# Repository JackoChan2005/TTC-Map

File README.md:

# TTC Map

A Toronto rail explorer and ESP32 LED display built around one transit-state API.
The web map shows Lines 1, 2, 4, 5 and 6 over OpenStreetMap, with route search,
station details, directional markers and a schematic view.

The project implements GTFS import and validation, bounded NTAS polling, estimated
train positions, a shared web/LED state model, the browser interface and firmware
for an eight-LED board revision. Contributor history is available in Git; individual
ownership and asset permissions are documented in [docs/ASSETS.md](docs/ASSETS.md).

The image records a real-data session on September 12, 2026; it is not a live feed.

```text
Toronto Open Data GTFS -> validated SQLite schedules/topology --+
TTC NTAS countdowns -> per-line snapshots and interpolation ----+-> map state
                                                               |-> web explorer
                                                               +-> ESP32 LED frame
```

Python/FastAPI serves the vanilla JavaScript/SVG frontend. SQLite, pandas and
HTTPX handle data; ESP-IDF/PlatformIO builds the firmware. There is no frontend
build step and no Node server.

## What the map means

- Filled arrows are NTAS-backed estimates; outlined arrows are scheduled estimates.
  Neither is GPS. Routes connect station coordinates approximately, not surveyed tracks.
- Lines 1/2/4 use NTAS when healthy. Line 5 is scheduled unless explicitly enabled
  after [coverage validation](docs/LINE_5_6.md); Line 6 is schedule-only.
- Direction follows API travel order. Unknown direction uses a neutral marker.
- Departures are scheduled, within a two-minute line-wide window capped at 200 rows.
  Service alerts, live station arrival boards and journey planning are unavailable.
- Data health does not imply normal TTC operations. Failed state requests clear
  train markers; a missing street background leaves the transit overlay usable.

## Run on Windows

Install [uv](https://docs.astral.sh/uv/getting-started/installation/), clone this
repository, then double-click `start.bat` or run it from PowerShell:

```powershell
.\start.bat
```

The launcher installs the locked dependencies and starts the server. It keeps
Python packages in `%LOCALAPPDATA%\TTC-Map\venv`, outside OneDrive. Python 3.13 is
selected by `.python-version`; uv can download it if needed. Do not repair or
reuse an old OneDrive-managed `.venv` to run this launcher.

Open <http://localhost:8000> for the map, `/search/` for timetable search, and
`/docs` or `/redoc` for the local interactive API reference. Stop with Ctrl+C.
For another port: `.\start.bat serve --port 8001`.

[Windows setup and clean-checkout verification](docs/SETUP.md) includes manual
commands, separate-checkout environments and offline rehearsal.

## macOS / Linux

Install [uv](https://docs.astral.sh/uv/getting-started/installation/), then open a
terminal in this repository and run:

```sh
./start.command
```

On macOS you can also double-click `start.command`. The launcher installs the
locked dependencies into `.venv` and starts the server. Open
<http://localhost:8000> and stop with Ctrl+C. Use
`./start.command serve --port 8001` for another port or `./start.command refresh`
for a feed check. If an extracted archive loses executable permissions, run
`bash start.command`.

Equivalent manual commands:

```sh
uv sync --locked
uv run --no-sync ttcmap serve
```

Python 3.12+ is supported by the package; the repository pins 3.13 for development.
Use one worker and a local SQLite database. Linux startup has been checked under
Ubuntu 24.04 (WSL2); macOS runtime and physical hardware validation remain separate
checks. See [setup verification](docs/SETUP.md#macos--linux).

## Commands

Run these after the platform-specific setup. On Windows, set
`$env:UV_PROJECT_ENVIRONMENT = "$env:LOCALAPPDATA\TTC-Map\venv"` first, or use
`.\start.bat refresh` for a feed check.

| Command | Purpose |
|---|---|
| `uv run --no-sync ttcmap refresh` | Check/rebuild the feed; add `--force` for a forced rebuild |
| `uv run --no-sync ttcmap build-network` | Regenerate exports from the verified cache |
| `uv run --no-sync pytest` | Backend tests |
| `uv run --no-sync ruff check src tests` | Python lint |
| `node --test tests/web/*.test.mjs` | Frontend unit tests, optional Node.js |
| `node scripts/build-schematic.mjs` | Regenerate schematic after network export |

Browser tests use a pinned optional Playwright install; see [SETUP.md](docs/SETUP.md).
There is no separate JavaScript build, type-checker or linter configured.

## API and structure

The local API reference reads `/openapi.json` and can send GET requests without
external scripts. All transit routes are below `/api/v1`:

| GET endpoint | Data |
|---|---|
| `/health`, `/gtfs/status` | Dataset and per-line source diagnostics |
| `/map-config` | Matching generation, network and schematic |
| `/network`, `/layout/{name}` | Topology or an individual layout |
| `/map-state` | Estimated positions; source and optional time selection |
| `/departures?route=1` | Scheduled departure window |
| `/led-state`, `/led-state.bin` | Board frame as JSON or packed bits |

Refresh is CLI-only. The former `POST /api/v1/gtfs/refresh` is removed so a viewer
cannot trigger an expensive rebuild. The web refresh button reloads read endpoints.

| Directory | Purpose |
|---|---|
| `src/ttcmap/` | API, GTFS pipeline, source selection and LED renderer |
| `web/` | Explorer, timetable and local API reference |
| `shared/` | Reviewed station identities and generated network/layout exports |
| `firmware/` | ESP-IDF firmware; local Wi-Fi settings are gitignored |
| `hardware/` | Integrated KiCad design and eight-LED board map |
| `tests/`, `scripts/` | Validation and schematic generation |
| `data/` | Ignored feeds, database, local validation and private asset archive |

Run from an editable repository checkout. A standalone wheel does not include the
web/shared/hardware resources and is not a supported deployment package.

## Configuration and troubleshooting

Copy `.env.example` to `.env` for optional overrides; all fields are in
`src/ttcmap/config.py`. Local paths resolve against the checkout. For OneDrive
installations that also need database isolation, configure `DATA_DIR` and `DB_PATH`
to local storage. Cloud synchronization is not multi-host database coordination.

- **Port occupied:** use another port with the launcher/CLI.
- **Transit data unavailable:** check `/api/v1/health` and refresh logs. First import,
  expired schedules or a failed upgrade can cause 503 responses.
- **Scheduled labels:** live observations may be unavailable or disabled for that line.
- **Street map unavailable:** use the schematic; OSM tiles are an external service.
- **Firmware connection:** follow [ESP32_SMOKE_TEST.md](docs/ESP32_SMOKE_TEST.md).
  The eight-LED revision does not represent a fully wired station network.

See [ARCHITECTURE.md](docs/ARCHITECTURE.md), [UI_API_AUDIT.md](docs/UI_API_AUDIT.md),
[validation results](docs/UI_VALIDATION.md) and [asset/publication status](docs/ASSETS.md).

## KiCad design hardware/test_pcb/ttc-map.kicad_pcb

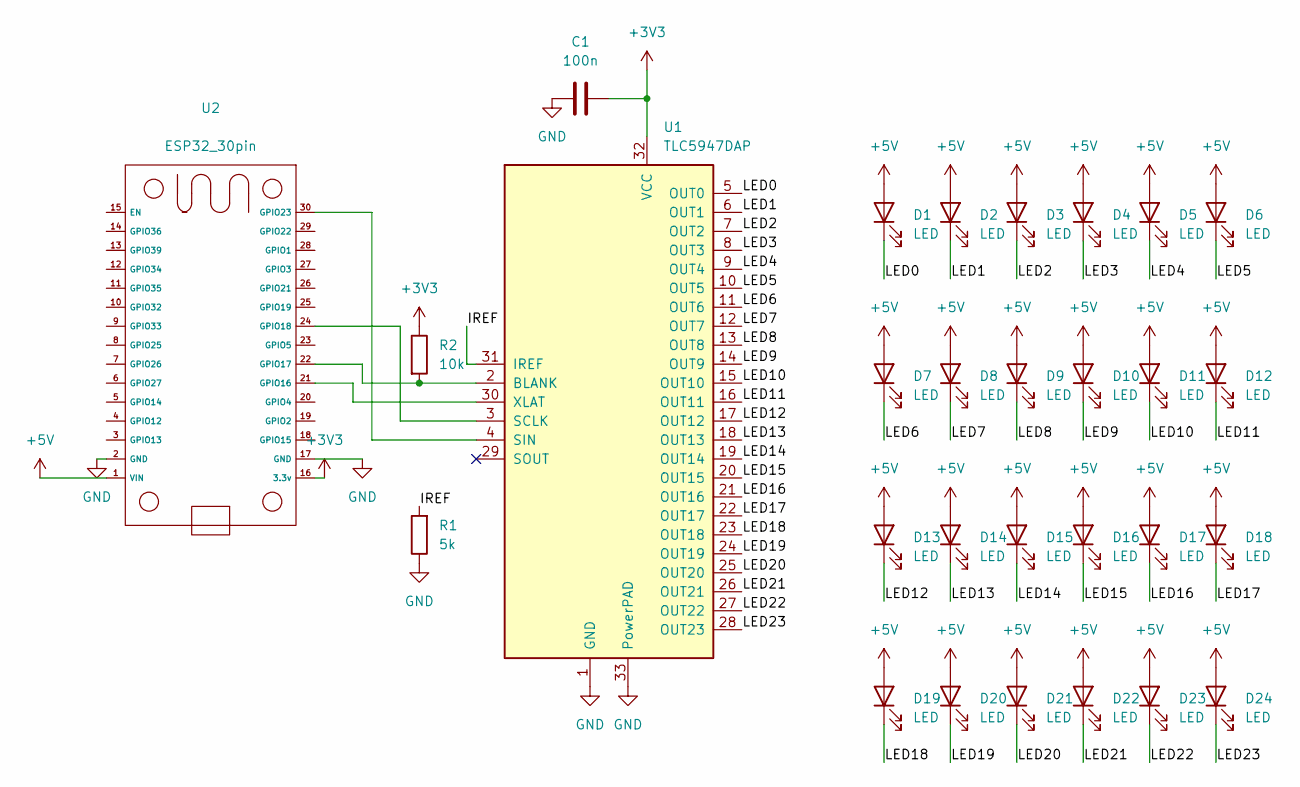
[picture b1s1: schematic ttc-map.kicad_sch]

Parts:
C1: 100n; C_0603_1608Metric_Pad1.08x0.95mm_HandSolder
D1, D2, D3, D4, D5, D6, D7, D8, D9, D10, D11, D12, D13, D14, D15, D16, D17, D18, D19, D20, D21, D22, D23, D24: LED; LED_0603_1608Metric_Pad1.05x0.95mm_HandSolder
R1: 5k; R_Axial_DIN0207_L6.3mm_D2.5mm_P7.62mm_Horizontal
R2: 10k; R_Axial_DIN0207_L6.3mm_D2.5mm_P7.62mm_Horizontal
U1: TLC5947DAP; HTSSOP-32-1EP_6.1x11mm_P0.65mm_EP5.2x11mm_Mask4.11x4.36mm_T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
U2: ESP32_30pin

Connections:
+3V3: C1.1, R2.1, U1.32 (VCC), U2.16 (3.3v)
+5V: D1.2 (A), D2.2 (A), D3.2 (A), D4.2 (A), D5.2 (A), D6.2 (A), D7.2 (A), D8.2 (A), D9.2 (A), D10.2 (A), D11.2 (A), D12.2 (A), D13.2 (A), D14.2 (A), D15.2 (A), D16.2 (A), D17.2 (A), D18.2 (A), D19.2 (A), D20.2 (A), D21.2 (A), D22.2 (A), D23.2 (A), D24.2 (A), U2.1 (VIN)
/IREF: R1.2, U1.31 (IREF)
/LED0: D1.1 (K), U1.5 (OUT0)
/LED1: D2.1 (K), U1.6 (OUT1)
/LED2: D3.1 (K), U1.7 (OUT2)
/LED3: D4.1 (K), U1.8 (OUT3)
/LED4: D5.1 (K), U1.9 (OUT4)
/LED5: D6.1 (K), U1.10 (OUT5)
/LED6: D7.1 (K), U1.11 (OUT6)
/LED7: D8.1 (K), U1.12 (OUT7)
/LED8: D9.1 (K), U1.13 (OUT8)
/LED9: D10.1 (K), U1.14 (OUT9)
/LED10: D11.1 (K), U1.15 (OUT10)
/LED11: D12.1 (K), U1.16 (OUT11)
/LED12: D13.1 (K), U1.17 (OUT12)
/LED13: D14.1 (K), U1.18 (OUT13)
/LED14: D15.1 (K), U1.19 (OUT14)
/LED15: D16.1 (K), U1.20 (OUT15)
/LED16: D17.1 (K), U1.21 (OUT16)
/LED17: D18.1 (K), U1.22 (OUT17)
/LED18: D19.1 (K), U1.23 (OUT18)
/LED19: D20.1 (K), U1.24 (OUT19)
/LED20: D21.1 (K), U1.25 (OUT20)
/LED21: D22.1 (K), U1.26 (OUT21)
/LED22: D23.1 (K), U1.27 (OUT22)
/LED23: D24.1 (K), U1.28 (OUT23)
GND: C1.2, R1.1, U1.1 (GND), U1.33 (PowerPAD), U2.2 (GND), U2.17 (GND)
unnamed: R2.2, U1.2 (BLANK), U2.22 (GPIO17)
unnamed: U1.3 (SCLK), U2.24 (GPIO18)
unnamed: U1.4 (SIN), U2.30 (GPIO23)
unnamed: U1.30 (XLAT), U2.21 (GPIO16)

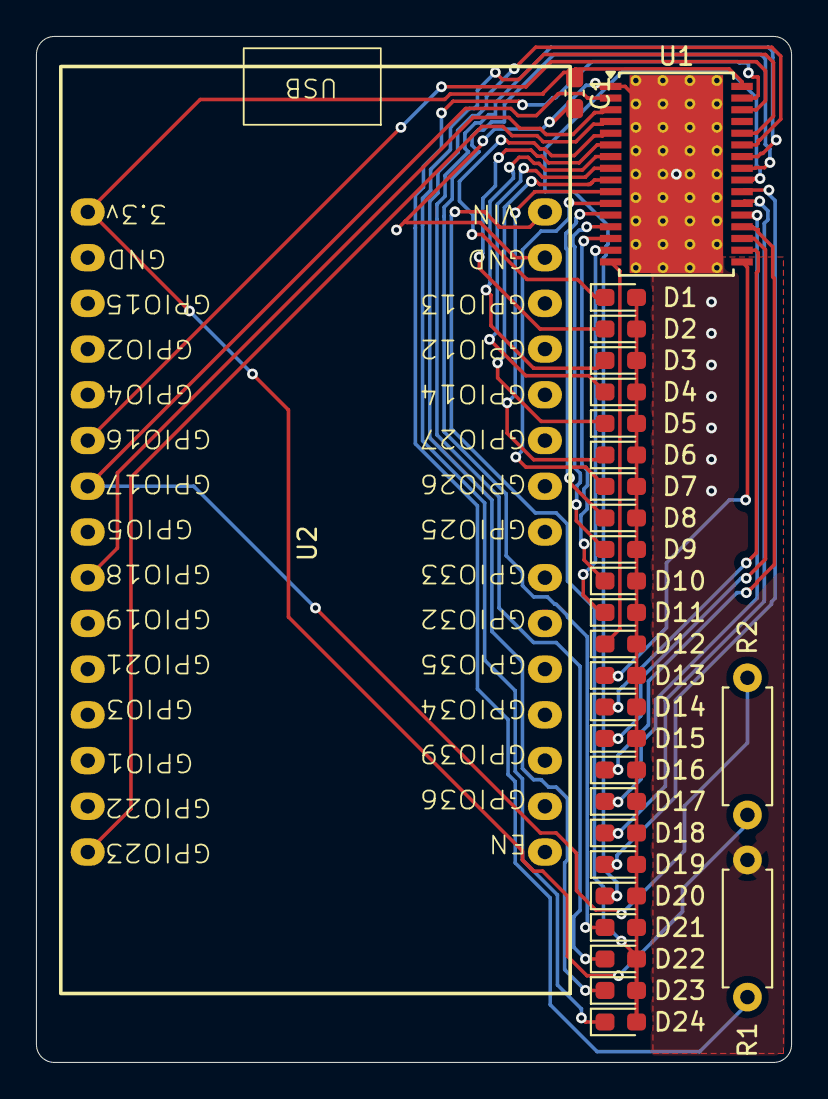
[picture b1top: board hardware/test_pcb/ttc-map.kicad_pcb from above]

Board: 2 copper layers, 42.0 x 57.0 mm, 29 parts (0 on the bottom side), 32 nets.

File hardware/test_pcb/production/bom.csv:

Designator,Footprint,Quantity,Value,LCSC Part #
C1,0603,1,100n,
"D1, D10, D11, D12, D13, D14, D15, D16, D17, D18, D19, D2, D20, D21, D22, D23, D24, D3, D4, D5, D6, D7, D8, D9",0603,24,LED,
R1,R_Axial_DIN0207_L6.3mm_D2.5mm_P7.62mm_Horizontal,1,5k,
R2,R_Axial_DIN0207_L6.3mm_D2.5mm_P7.62mm_Horizontal,1,10k,
U1,HTSSOP-32-1EP_6.1x11mm_P0.65mm_EP5.2x11mm_Mask4.11x4.36mm_ThermalVias,1,TLC5947DAP,
U2,ESP32_30pin,1,~,

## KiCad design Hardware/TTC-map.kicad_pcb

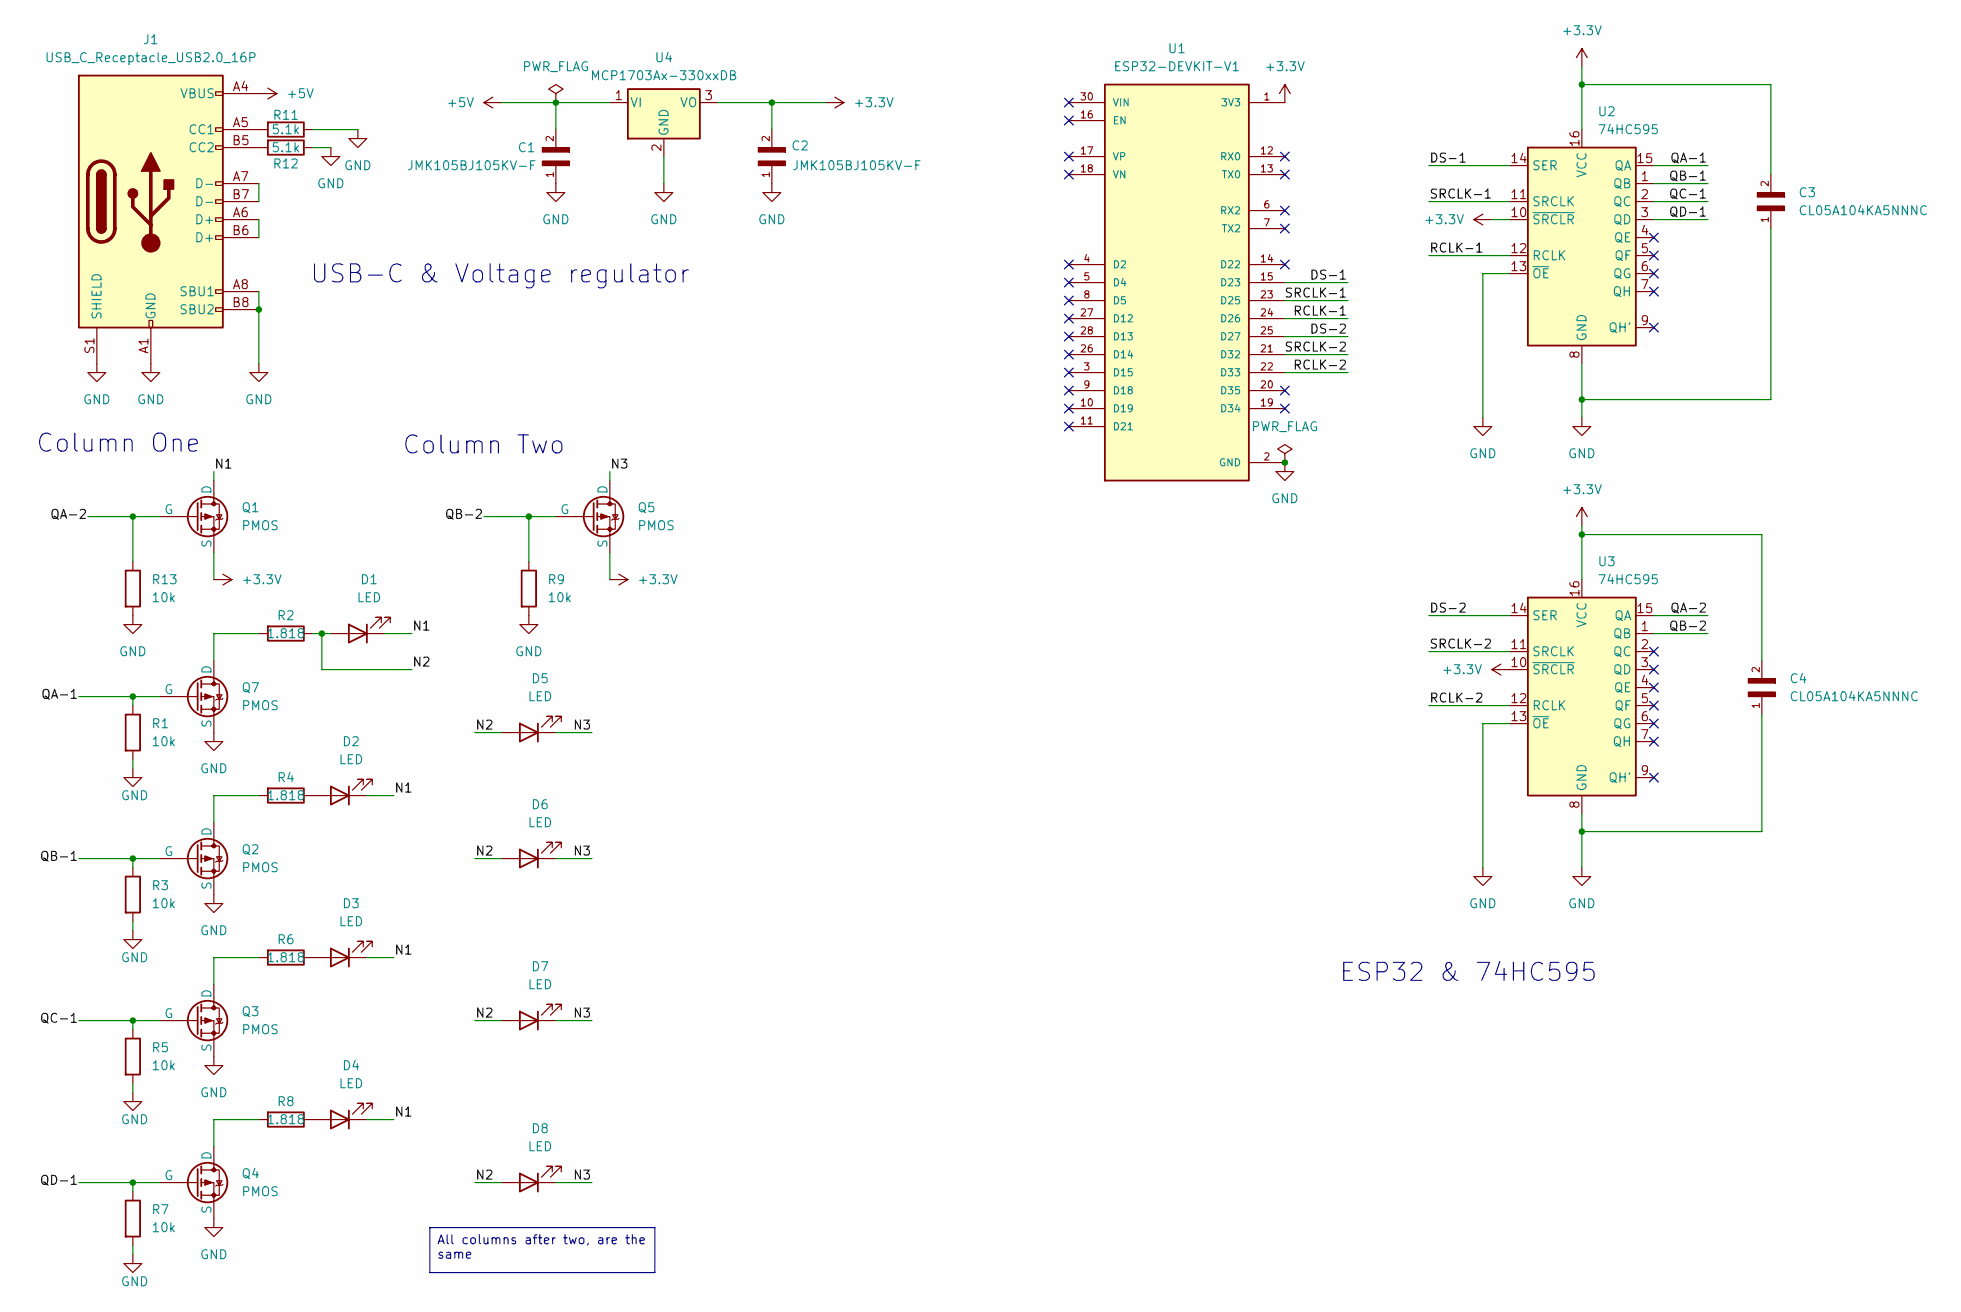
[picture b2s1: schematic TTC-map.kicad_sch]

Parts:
C1, C2: JMK105BJ105KV-F; CAPC1005X55N
C3, C4: CL05A104KA5NNNC; CAPC1005X55N
D1, D2, D3, D4, D5, D6, D7, D8: LED; LED_D3.0mm
J1: USB_C_Receptacle_USB2.0_16P; USB_C_Receptacle_GCT_USB4105-xx-A_16P_TopMnt_Horizontal
Q1, Q2, Q3, Q4, Q5, Q7: PMOS; SOT95P240X120-3N
R1, R3, R5, R7, R9, R13: 10k; R_0805_2012Metric
R2, R4, R6, R8: 1.818; R_0805_2012Metric
R11, R12: 5.1k; R_0805_2012Metric
U1: ESP32-DEVKIT-V1; MODULE_ESP32_DEVKIT_V1; PARTREV N/A
U2, U3: 74HC595; SOIC127P600X175-16N
U4: MCP1703Ax-330xxDB; SOT-223-3_TabPin2

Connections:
+3.3V: C2.2, C3.2, C4.2, Q1.3 (S), Q5.3 (S), U1.1 (3V3), U2.10 (~SRCLR), U2.16 (VCC), U3.10 (~SRCLR), U3.16 (VCC), U4.3 (VO)
+5V: C1.2, J1.A4 (VBUS), J1.A9 (VBUS), J1.B4 (VBUS), J1.B9 (VBUS), U4.1 (VI)
/DS-1: U1.15 (D23), U2.14 (SER)
/DS-2: U1.25 (D27), U3.14 (SER)
/N1: D1.1 (K), D2.1 (K), D3.1 (K), D4.1 (K), Q1.1 (D)
/N2: D1.2 (A), D5.2 (A), D6.2 (A), D7.2 (A), D8.2 (A), R2.1
/N3: D5.1 (K), D6.1 (K), D7.1 (K), D8.1 (K), Q5.1 (D)
/QA-1: Q7.2 (G), R1.1, U2.15 (QA)
/QA-2: Q1.2 (G), R13.1, U3.15 (QA)
/QB-1: Q2.2 (G), R3.1, U2.1 (QB)
/QB-2: Q5.2 (G), R9.1, U3.1 (QB)
/QC-1: Q3.2 (G), R5.1, U2.2 (QC)
/QD-1: Q4.2 (G), R7.1, U2.3 (QD)
/RCLK-1: U1.24 (D26), U2.12 (RCLK)
/RCLK-2: U1.22 (D33), U3.12 (RCLK)
/SRCLK-1: U1.23 (D25), U2.11 (SRCLK)
/SRCLK-2: U1.21 (D32), U3.11 (SRCLK)
GND: C1.1, C2.1, C3.1, C4.1, J1.A1 (GND), J1.A8 (SBU1), J1.A12 (GND), J1.B1 (GND), J1.B8 (SBU2), J1.B12 (GND), J1.S1 (SHIELD), Q2.3 (S), Q3.3 (S), Q4.3 (S), Q7.3 (S), R1.2, R3.2, R5.2, R7.2, R9.2, R11.1, R12.1, R13.2, U1.2 (GND), U1.29 (GND), U2.8 (GND), U2.13 (~OE), U3.8 (GND), U3.13 (~OE), U4.2 (GND)
unnamed: D2.2 (A), R4.1
unnamed: D3.2 (A), R6.1
unnamed: D4.2 (A), R8.1
unnamed: J1.A5 (CC1), R11.2
unnamed: J1.B5 (CC2), R12.2
unnamed: J1.A6 (D+), J1.B6 (D+)
unnamed: J1.A7 (D-), J1.B7 (D-)
unnamed: Q2.1 (D), R4.2
unnamed: Q3.1 (D), R6.2
unnamed: Q4.1 (D), R8.2
unnamed: Q7.1 (D), R2.2

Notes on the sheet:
USB-C & Voltage regulator
Column Two
ESP32 & 74HC595
Column One
All columns after two, are the same

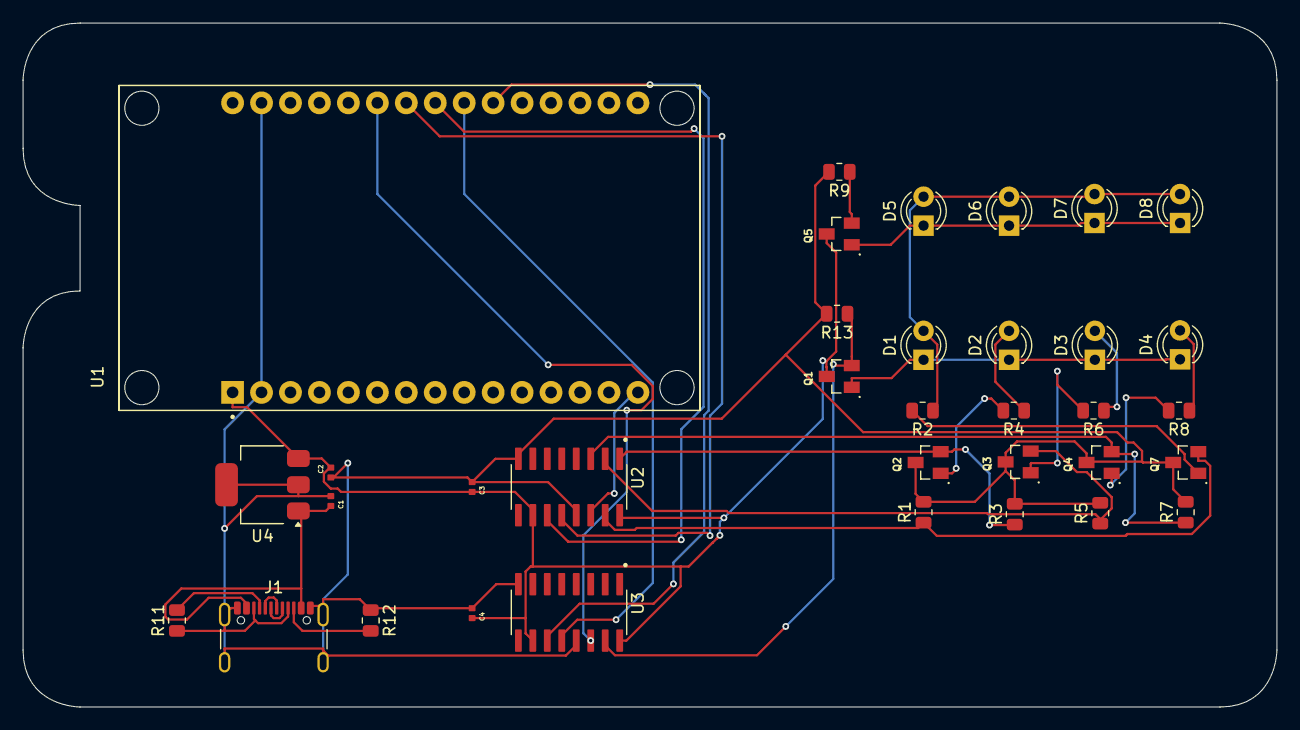
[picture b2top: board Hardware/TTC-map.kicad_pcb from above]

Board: 2 copper layers, 110.0 x 60.0 mm, 35 parts (0 on the bottom side), 29 nets.

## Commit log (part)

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2026-01-23 Add trial JSON data for Downsview Station
    Added JSON structure for Downsview Station including stops, routes, and service times.
2026-01-25 Initial API code
2026-01-25 Add gitignore
2026-01-25 Updated gitignore
2026-01-25 removed json
2026-01-25 Basic API implementation complete
2026-01-25 Created README and requirements files
2026-01-26 Created new API functions, Created update_db class
2026-01-26 Reorganized files + Fixed minor syntax error
2026-01-26 Update README.md for clarity and formatting
    Correct formatting and remove unnecessary text.
2026-01-27 Made update excutable
2026-01-27 Update README with additional setup steps
    Added instructions for moving to the src directory and running update_db.py.
2026-01-27 Update README instructions for clarity and formatting
2026-02-05 Added hardware designs
2026-02-07 Rerouted the PCB
2026-02-13 Add node-api files
2026-02-13 Update gitignore
2026-02-13 ESP Code
2026-02-13 Remove unwanted files
2026-02-13 removed unwanted file
2026-02-13 Remove local data artifacts
2026-02-13 Update node-api reference
2026-02-13 Convert node-api to regular tracked folder
2026-02-14 Updated .env file
2026-02-14 added wifi connection for ESP32
2026-02-14 set up bash script
2026-02-14 Made setup agnostic
2026-02-16 added 3d step files to the 3d pcb viewer
2026-06-10 made api changes
2026-06-12 Revert "Add dark-mode Command Center dashboard at /command/"
    This reverts commit 2924f56c1296bd9e12712f993422b39abae7b2c6.
